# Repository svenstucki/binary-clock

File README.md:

Binary Clock
============

This repo contains the source files for my self made binary clock. It uses a TI
BQ32000 real-time clock chip for time keeping, a TI TLC5928 LED driver for the
LEDs and an Atmel AtTiny24A microcontroller to control it.

The pcb/ folder contains the schemtaic and board layout (made with EAGLE). The
firmware and source code for the Atmel microcontroller can be found in the code/
folder.

The v1 board layout contains some errors. The footprint for the LDO is wrong
and connects +3V3 to GND. Also I forgot to add a decoupling capacitor for the
RTC. You can work around this by isolating the big tab of the LDO from GND, the
RTC functions without decoupling. Version 2 fixes those errors.

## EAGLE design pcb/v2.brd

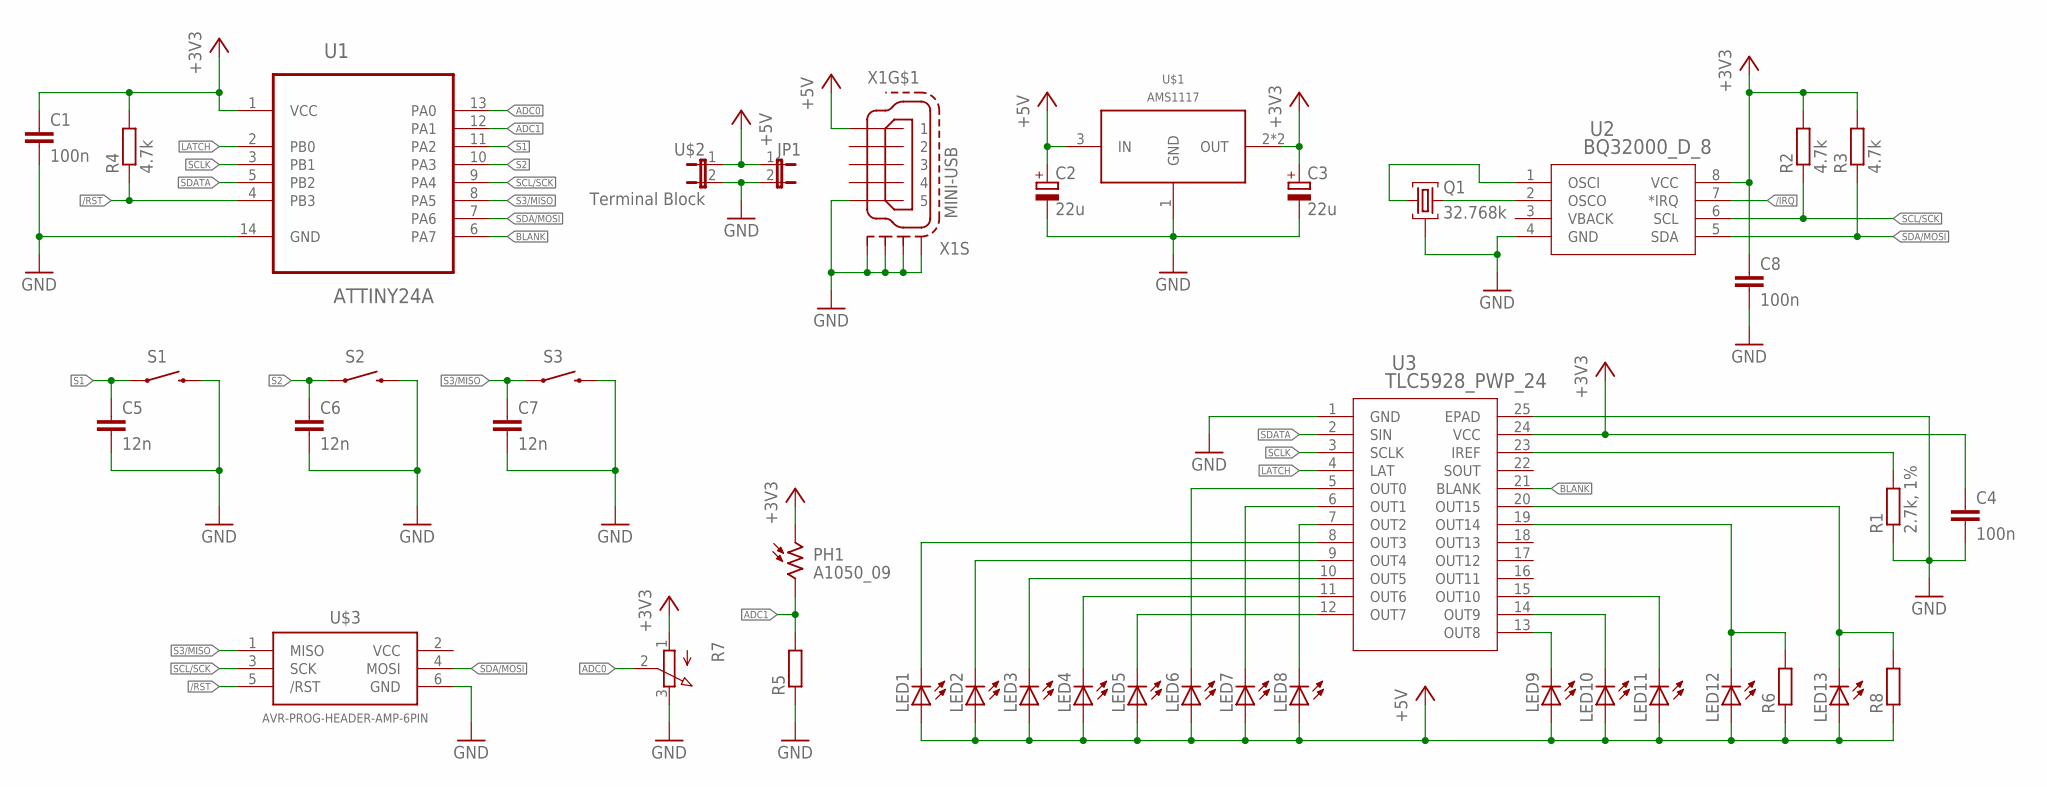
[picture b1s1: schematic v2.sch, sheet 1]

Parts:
C1, C4, C8: 100n; C0603
C2, C3: 22u; 153CLV-0505
C5, C6, C7: 12n; C0603
JP1: JP1E; JP1
LED1, LED2, LED3, LED4, LED5, LED6, LED7, LED8, LED9, LED10, LED11, LED12, LED13: LEDCHIP-LED0603; CHIP-LED0603
PH1: A1050_09; T0-46-A10XX
Q1: 32.768k; TC38
R1: 2.7k, 1%; R1206
R2, R3, R4: 4.7k; R0603
R5, R6, R8: R-EU_R0603; R0603
R7: 3RP/1610N
S1, S2, S3: SWITCH-MOMENTARY-2PTH; TACTILE-PTH
U1: ATTINY24A; SOIC127P600X175-14N
U2: BQ32000_D_8; D8
U3: TLC5928_PWP_24; PWP24_4P87X2P4
U$1: AMS1117; DCY4
U$2: Terminal Block; BASTLI_SCREW_TERMINAL_SMALL
U$3: AVR-PROG-HEADER-AMP-6PIN; AMP-TMM-1-0-06
X1: MINI-USB; 32005-201

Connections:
+3V3: C1.1, C3.+, C4.1, C8.1, PH1.1, R2.2, R3.2, R4.2, R7.1 (A), U1.1 (VCC), U2.8 (VCC), U3.24 (VCC), U$1.2 (OUT), U$1.4 (OUT)
+5V: C2.+, JP1.1, LED1.A, LED2.A, LED3.A, LED4.A, LED5.A, LED6.A, LED7.A, LED8.A, LED9.A, LED10.A, LED11.A, LED12.A, LED13.A, R6.1, R8.1, U$1.3 (IN), U$2.1, X1.1
/IRQ: U2.7 (*IRQ)
/RST: R4.1, U1.4 (PB3), U$3.5 (/RST)
ADC0: R7.2 (S), U1.13 (PA0)
ADC1: PH1.2, R5.2, U1.12 (PA1)
BLANK: U1.6 (PA7), U3.21 (BLANK)
GND: C1.2, C2.-, C3.-, C4.2, C5.2, C6.2, C7.2, C8.2, JP1.2, Q1.1 (2), R1.1, R5.1, R7.3 (E), S1.3 (2), S2.3 (2), S3.3 (2), U1.14 (GND), U2.4 (GND), U3.1 (GND), U3.25 (EPAD), U$1.1 (GND), U$2.2, U$3.6 (GND), X1.5, X1.M1 (S1), X1.M2 (S2), X1.M3 (S3), X1.M4 (S4); also elsewhere on the board
LATCH: U1.2 (PB0), U3.4 (LAT)
unnamed: LED1.C, U3.8 (OUT3)
unnamed: LED2.C, U3.9 (OUT4)
unnamed: LED3.C, U3.10 (OUT5)
unnamed: LED4.C, U3.11 (OUT6)
unnamed: LED5.C, U3.12 (OUT7)
unnamed: R1.2, U3.23 (IREF)
unnamed: LED6.C, U3.5 (OUT0)
unnamed: LED7.C, U3.6 (OUT1)
unnamed: LED8.C, U3.7 (OUT2)
unnamed: LED9.C, U3.13 (OUT8)
unnamed: LED10.C, U3.14 (OUT9)
unnamed: LED11.C, U3.15 (OUT10)
unnamed: LED12.C, R6.2, U3.19 (OUT14)
unnamed: LED13.C, R8.2, U3.20 (OUT15)
unnamed: Q1.3, U2.2 (OSCO)
unnamed: Q1.2 (1), U2.1 (OSCI)
S1: C5.1, S1.1, U1.11 (PA2)
S2: C6.1, S2.1, U1.10 (PA3)
S3/MISO: C7.1, S3.1, U1.8 (PA5), U$3.1 (MISO)
SCL/SCK: R2.1, U1.9 (PA4), U2.6 (SCL), U$3.3 (SCK)
SCLK: U1.3 (PB1), U3.3 (SCLK)
SDA/MOSI: R3.1, U1.7 (PA6), U2.5 (SDA), U$3.4 (MOSI)
SDATA: U1.5 (PB2), U3.2 (SIN)
VBACK: U2.3 (VBACK)

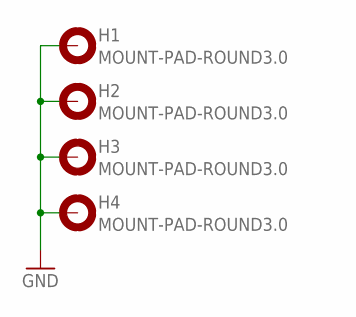
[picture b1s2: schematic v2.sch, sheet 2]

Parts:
H1, H2, H3, H4: MOUNT-PAD-ROUND3.0; 3,0-PAD

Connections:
GND: H1.B3,0, H2.B3,0, H3.B3,0, H4.B3,0; also elsewhere on the board

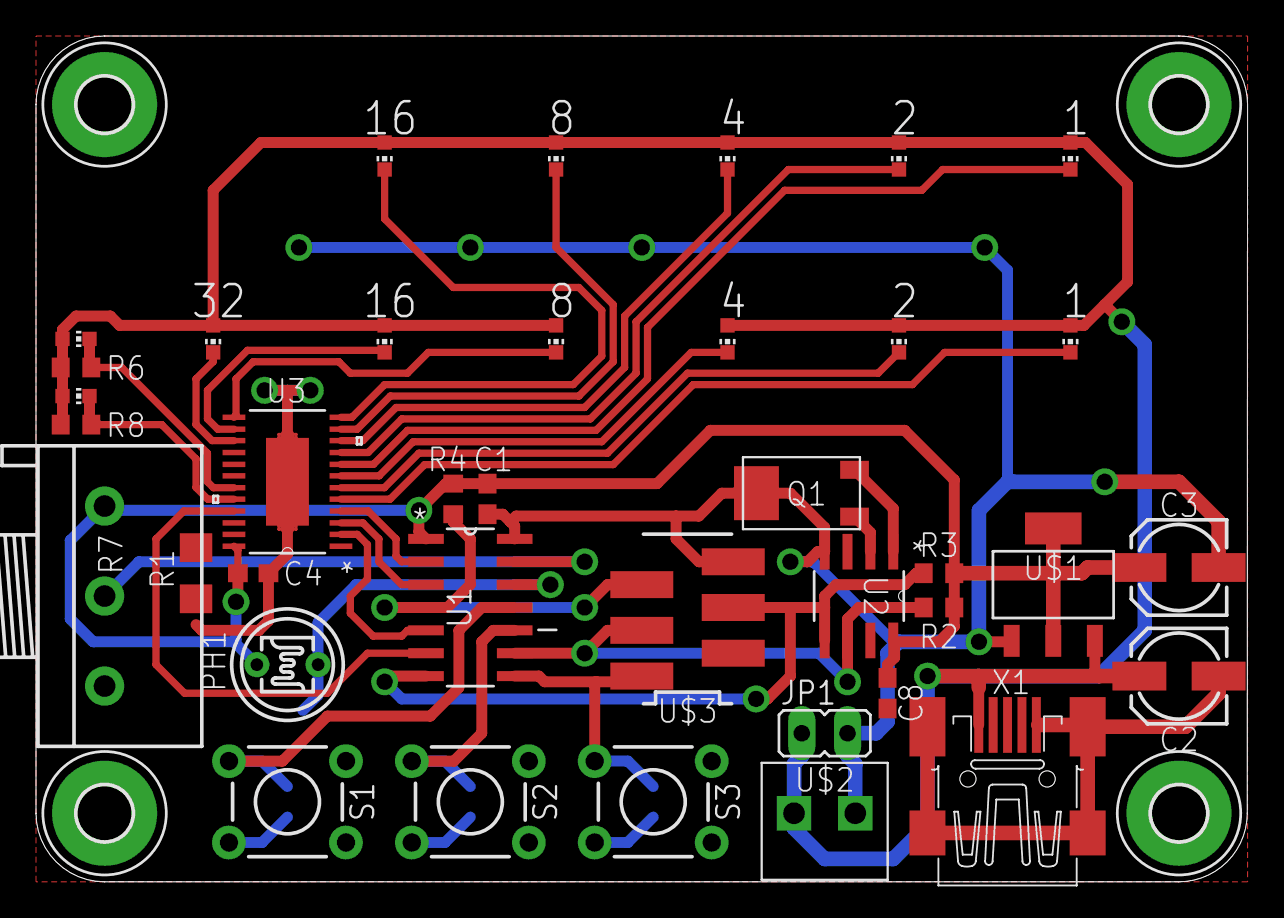
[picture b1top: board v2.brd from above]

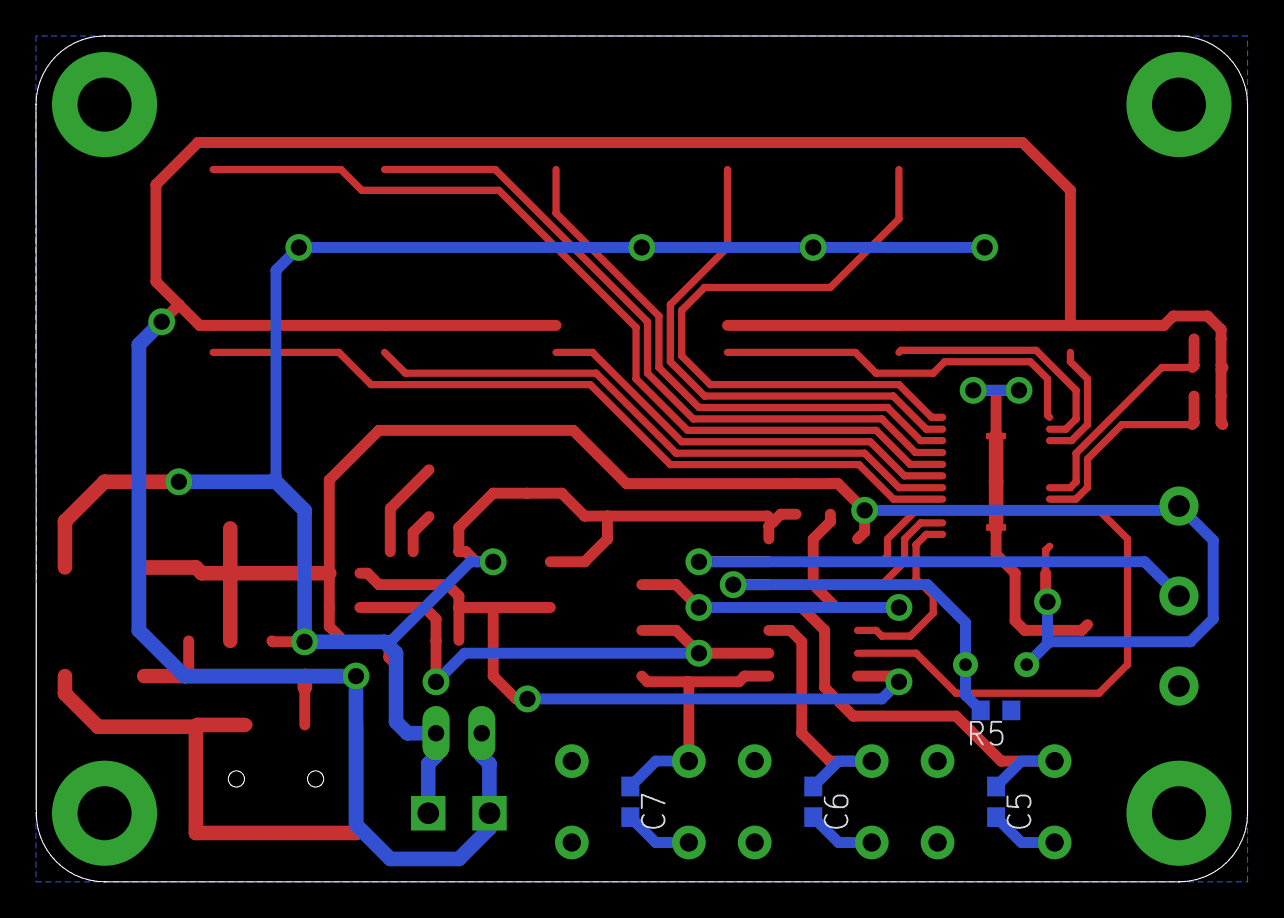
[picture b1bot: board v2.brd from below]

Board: 2 copper layers, 67.3 x 47.0 mm, 46 parts (4 on the bottom side), 31 nets.

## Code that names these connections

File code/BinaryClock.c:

/*
 * BinaryClock.c
 *
 * Created: 13.03.2014 15:29:36
 *  Author: Sven Stucki
 */


#include <avr/io.h>
#include <avr/interrupt.h>
#include <inttypes.h>

#include <util/delay.h>

#include "USI_TWI_Master.h"


/* this macro reorders the bits of a uint16_t so they correspond to the order of the LEDs on the board */
#define LED_ORDER(x)	( ((x) & 0xE0) >> 5 | ((x) & 0x1F) << 3 | ((x) & 0xFF00) )


/* application state */

/* 0 - normal, 1 - set hour, 2 - set minute */
uint8_t mode = 0;

/* current time*/
uint8_t time_h = 0, time_m = 0;

uint8_t tick_odd = 0;


/* application logic forward declaration */
void s1();
void s2();
void s3();
void tick();


uint16_t led_state = 0x0000;

/* send new LED state to LED driver */
void set_leds(uint16_t in) {
	unsigned int i;
	
	/* save new state in global */
	led_state = in;
	
	/* make sure latch is low */
	PORTB &= ~(1 << PB0);
	
	for (i = 0; i < 16; i++) {
		/* set clock to low */
		PORTB &= ~(1 << PB1);
		
		/* send bit */
		if (in & 0x8000) {
			PORTB |= (1 << PB2);
		} else {
			PORTB &= ~(1 << PB2);
		}
		
		/* set clock to high */
		PORTB |= (1 << PB1);
		
		/* move to next bit */
		in <<= 1;
	}
	
	/* send latch pulse */
	PORTB |= (1 << PB0);
	PORTB &= ~(1 << PB0);
}


/* interrupt handling */

uint8_t btns_prev;

ISR(PCINT0_vect) {
	uint8_t btns = PINA ^ btns_prev;
	btns_prev = PINA;
	
	if ((PINA & (1 << PA2)) == 0 && (btns & (1 << PA2)) != 0) {
		/* S1 pressed */
		s1();
	}
	if ((PINA & (1 << PA3)) == 0 && (btns & (1 << PA3)) != 0) {
		/* S2 pressed */
		s2();
	}
	if ((PINA & (1 << PA5)) == 0 && (btns & (1 << PA5)) != 0) {
		/* S3 pressed */
		s3();
	}
}

ISR(TIM1_COMPA_vect) {
	tick();
}

ISR(ADC_vect) {
	OCR0B = ADCH >> 1;
	ADCSRA |= (1 << ADSC);
}


#define RTC_ADDRESS	0xD0

void update_time() {
	unsigned char i2c_buffer[3];
	
	/* select minutes register */
	i2c_buffer[0] = RTC_ADDRESS | 0;	// write
	i2c_buffer[1] = 0x01;
	USI_TWI_Start_Transceiver_With_Data(i2c_buffer, 2);
	
	/* read minute and hour register */
	i2c_buffer[0] = RTC_ADDRESS | 1;	// read
	USI_TWI_Start_Transceiver_With_Data(i2c_buffer, 3);
	
	/* convert BCD digits to number */
	unsigned char minute_bcd = i2c_buffer[1];
	time_m = ((minute_bcd >> 4) & 0x07) * 10 + (minute_bcd & 0x0F);
	unsigned char hour_bcd = i2c_buffer[2];
	time_h = ((hour_bcd >> 4) & 0x03) * 10 + (hour_bcd & 0x0F);
}

void set_time() {
	unsigned char i2c_buffer[5];
	i2c_buffer[0] = RTC_ADDRESS | 0;	// write
	i2c_buffer[1] = 0x00;	// seconds register (followed by minute, then hour)
	i2c_buffer[2] = 0x00;	// set seconds to 0
	
	/* convert minute to BCD */
	i2c_buffer[3] = 0;
	i2c_buffer[3] |= (((time_m / 10) % 10) & 0x07) << 4;
	i2c_buffer[3] |= (time_m % 10) & 0x0F;
	
	/* convert hour to BCD */
	i2c_buffer[4] = 0;
	i2c_buffer[4] |= (((time_h / 10) % 10) & 0x03) << 4;
	i2c_buffer[4] |= (time_h % 10) & 0x0F;
	
	USI_TWI_Start_Transceiver_With_Data(i2c_buffer, 5);
}


int main(void) {
	/* disable /8 system clock prescaler */
	CLKPR = 0x80;
	CLKPR = 0x00;
	
	/* setup port directions */
	DDRA = (1 << DDA7);
	DDRB = (1 << DDB0) | (1 << DDB1) | (1 << DDB2);
	
	/* enable pull-ups for buttons */
	PORTA |= (1 << PA2) | (1 << PA3) | (1 << PA5);
	
	USI_TWI_Master_Initialise();

	/* activate LEDs */
	//PORTA &= ~(1 << PA7);
	
	/* prepare and start timer 0 LED PWM */
	TCCR0A = (1 << COM0B1) | (1 << COM0B0) | (1 << WGM01) | (1 << WGM00);
	TCCR0B = (0 << WGM02) | (0 << CS02) | (0 << CS01) | (1 << CS00);
	OCR0B = 0xA0;
	
	/* prepare and start timer 1 for 2 Hz interrupt */
	TCCR1A = 0x00;
	TCCR1B = (1 << WGM12) | (1 << CS11) | (1 << CS10);	// CTC mode, /64 prescale
	TCCR1C = 0x00;
	OCR1A = 0xF424;		// count to 62500 -> exactly 2 Hz
	TIMSK1 = (1 << OCIE1A);
	
	/* prepare and enable button interrupts */
	btns_prev = PINA;
	PCMSK0 = (1 << PCINT2) | (1 << PCINT3) | (1 << PCINT5);
	GIMSK = 0x10;
	
	/* prepare and start ADC */
	ADMUX = (1 << MUX0);
	ADCSRA = (1 << ADEN) | (1 << ADSC) | (1 << ADIE) | (1 << ADPS2) | (1 << ADPS1) | (1 << ADPS0);
	ADCSRB = (1 << ADLAR);
	
	/* enable global interrupts */
	sei();
	
	while(1);
		return 0;
}


/* application logic */

void s1() {
	mode = (mode + 1) % 3;
}

void s2() {
	if (mode == 1) {
		/* increase hour */
		time_h++;
		if (time_h >= 24) {
			time_h = 0;
		}
	} else if (mode == 2) {
		/* increase minute */
		time_m++;
		if (time_m >= 60) {
			time_m = 0;
			time_h++;
			if (time_h >= 24) {
				time_h = 0;
			}
		}
	}
}

void s3() {
	if (mode == 1) {
		/* decrease hour */
		if (time_h == 0) {
			time_h = 23;
		} else {
			time_h--;
		}
	} else if (mode == 2) {
		/* decrease minute */
		if (time_m == 0) {
			if (time_h == 0) {
				time_h = 23;
			} else {
				time_h--;
			}
			time_m = 59;
		} else {
			time_m--;
		}
	}
}


void tick() {
	tick_odd++;
	
	uint16_t leds = 0;
	if (mode == 0) {
		/* display time */
		update_time();
		leds = LED_ORDER((time_m << 5) | time_h);
	} else if (mode == 1) {
		/* flash hour */
		set_time();
		if (tick_odd % 2 == 0) {
			leds = LED_ORDER(time_m << 5);
		} else {
			leds = LED_ORDER((time_m << 5) | time_h);
		}
		leds |= 0x8000;
	} else if (mode == 2) {
		/* flash minute */
		set_time();
		if (tick_odd % 2 == 0) {
			leds = LED_ORDER(time_h);
		} else {
			leds = LED_ORDER((time_m << 5) | time_h);
		}
		leds |= 0x4000;
	}
	set_leds(leds);
}

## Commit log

2014-03-30 Added code to repo
2014-03-30 Added EAGLE files
2015-08-09 Minor cleanup

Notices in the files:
parts and their libraries:
SparkFun-Electromechanical: Licensing: CC v3.0 Share-Alike You are welcome to use this library for commercial purposes.
